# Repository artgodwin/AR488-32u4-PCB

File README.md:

# AR488-32u4-PCB
Kicad PCB layout for AR488 using an arduino pro-micro 32u4 board

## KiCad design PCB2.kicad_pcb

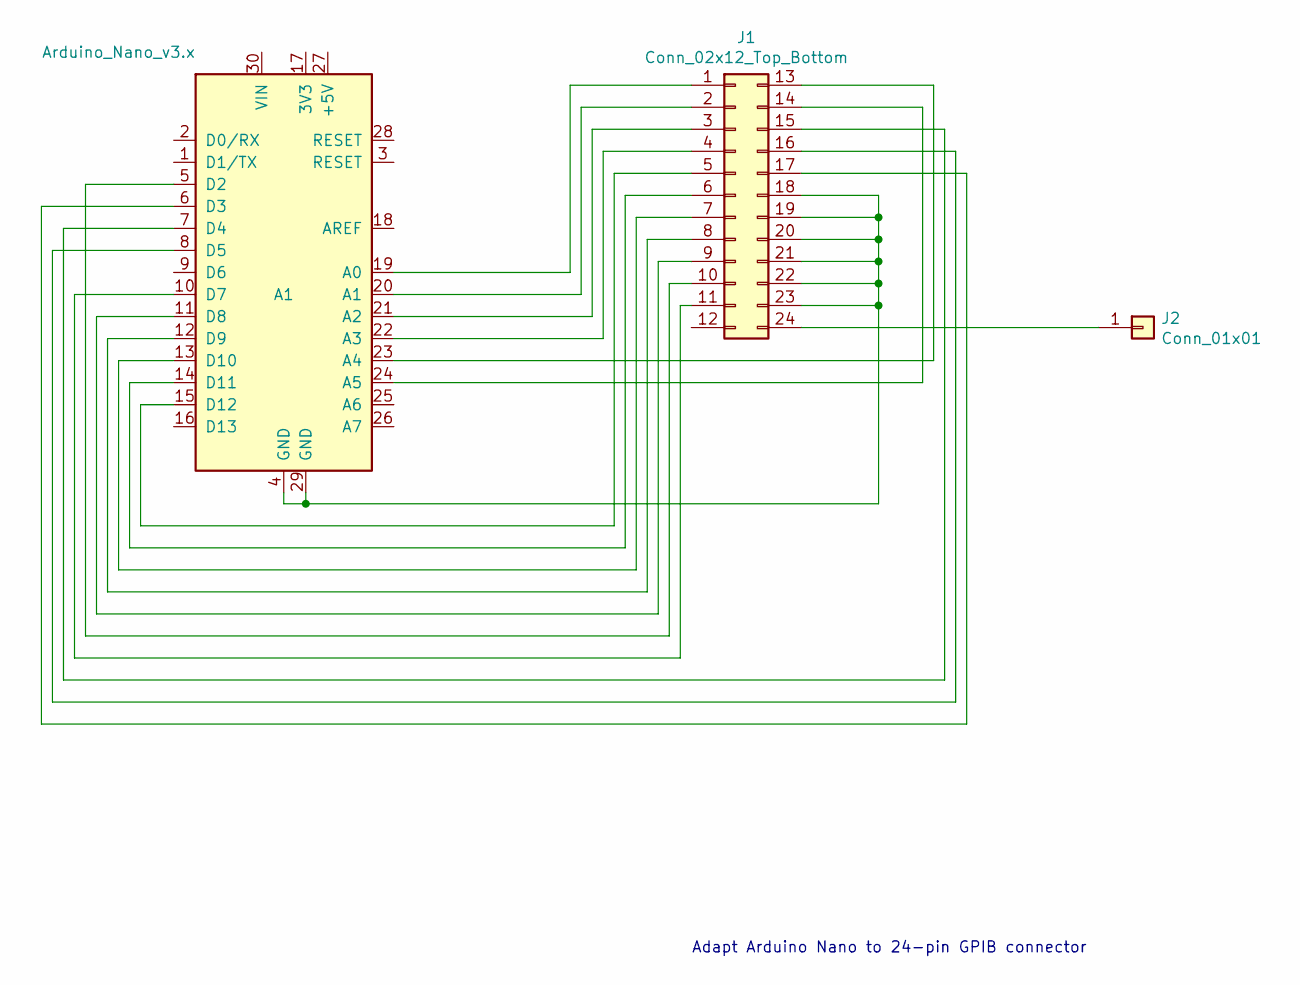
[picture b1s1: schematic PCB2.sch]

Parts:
A1: Arduino_Nano_v3.x; Arduino_Nano
J1: Conn_02x12_Top_Bottom; Microribbon-24
J2: Conn_01x01; PinHeader_1x01_P1.00mm_Horizontal

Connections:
unnamed: A1.5 (D2), J1.10
unnamed: A1.6 (D3), J1.17
unnamed: A1.7 (D4), J1.15
unnamed: A1.8 (D5), J1.16
unnamed: A1.10 (D7), J1.11
unnamed: A1.11 (D8), J1.9
unnamed: A1.12 (D9), J1.8
unnamed: A1.13 (D10), J1.7
unnamed: A1.14 (D11), J1.6
unnamed: A1.15 (D12), J1.5
unnamed: A1.19 (A0), J1.1
unnamed: A1.20 (A1), J1.2
unnamed: A1.21 (A2), J1.3
unnamed: A1.22 (A3), J1.4
unnamed: A1.23 (A4), J1.13
unnamed: A1.24 (A5), J1.14
unnamed: A1.4 (GND), A1.29 (GND), J1.18, J1.19, J1.20, J1.21, J1.22, J1.23
unnamed: J1.24, J2.1

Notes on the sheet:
Adapt Arduino Nano to 24-pin GPIB connector

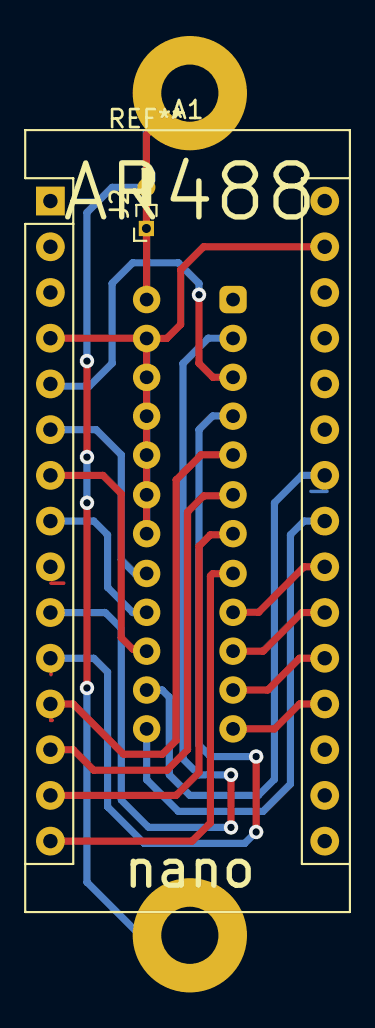
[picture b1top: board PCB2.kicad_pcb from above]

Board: 2 copper layers, 3 parts (1 on the bottom side), 18 nets.

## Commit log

2021-10-18 First entry to public git. May contain path errors
